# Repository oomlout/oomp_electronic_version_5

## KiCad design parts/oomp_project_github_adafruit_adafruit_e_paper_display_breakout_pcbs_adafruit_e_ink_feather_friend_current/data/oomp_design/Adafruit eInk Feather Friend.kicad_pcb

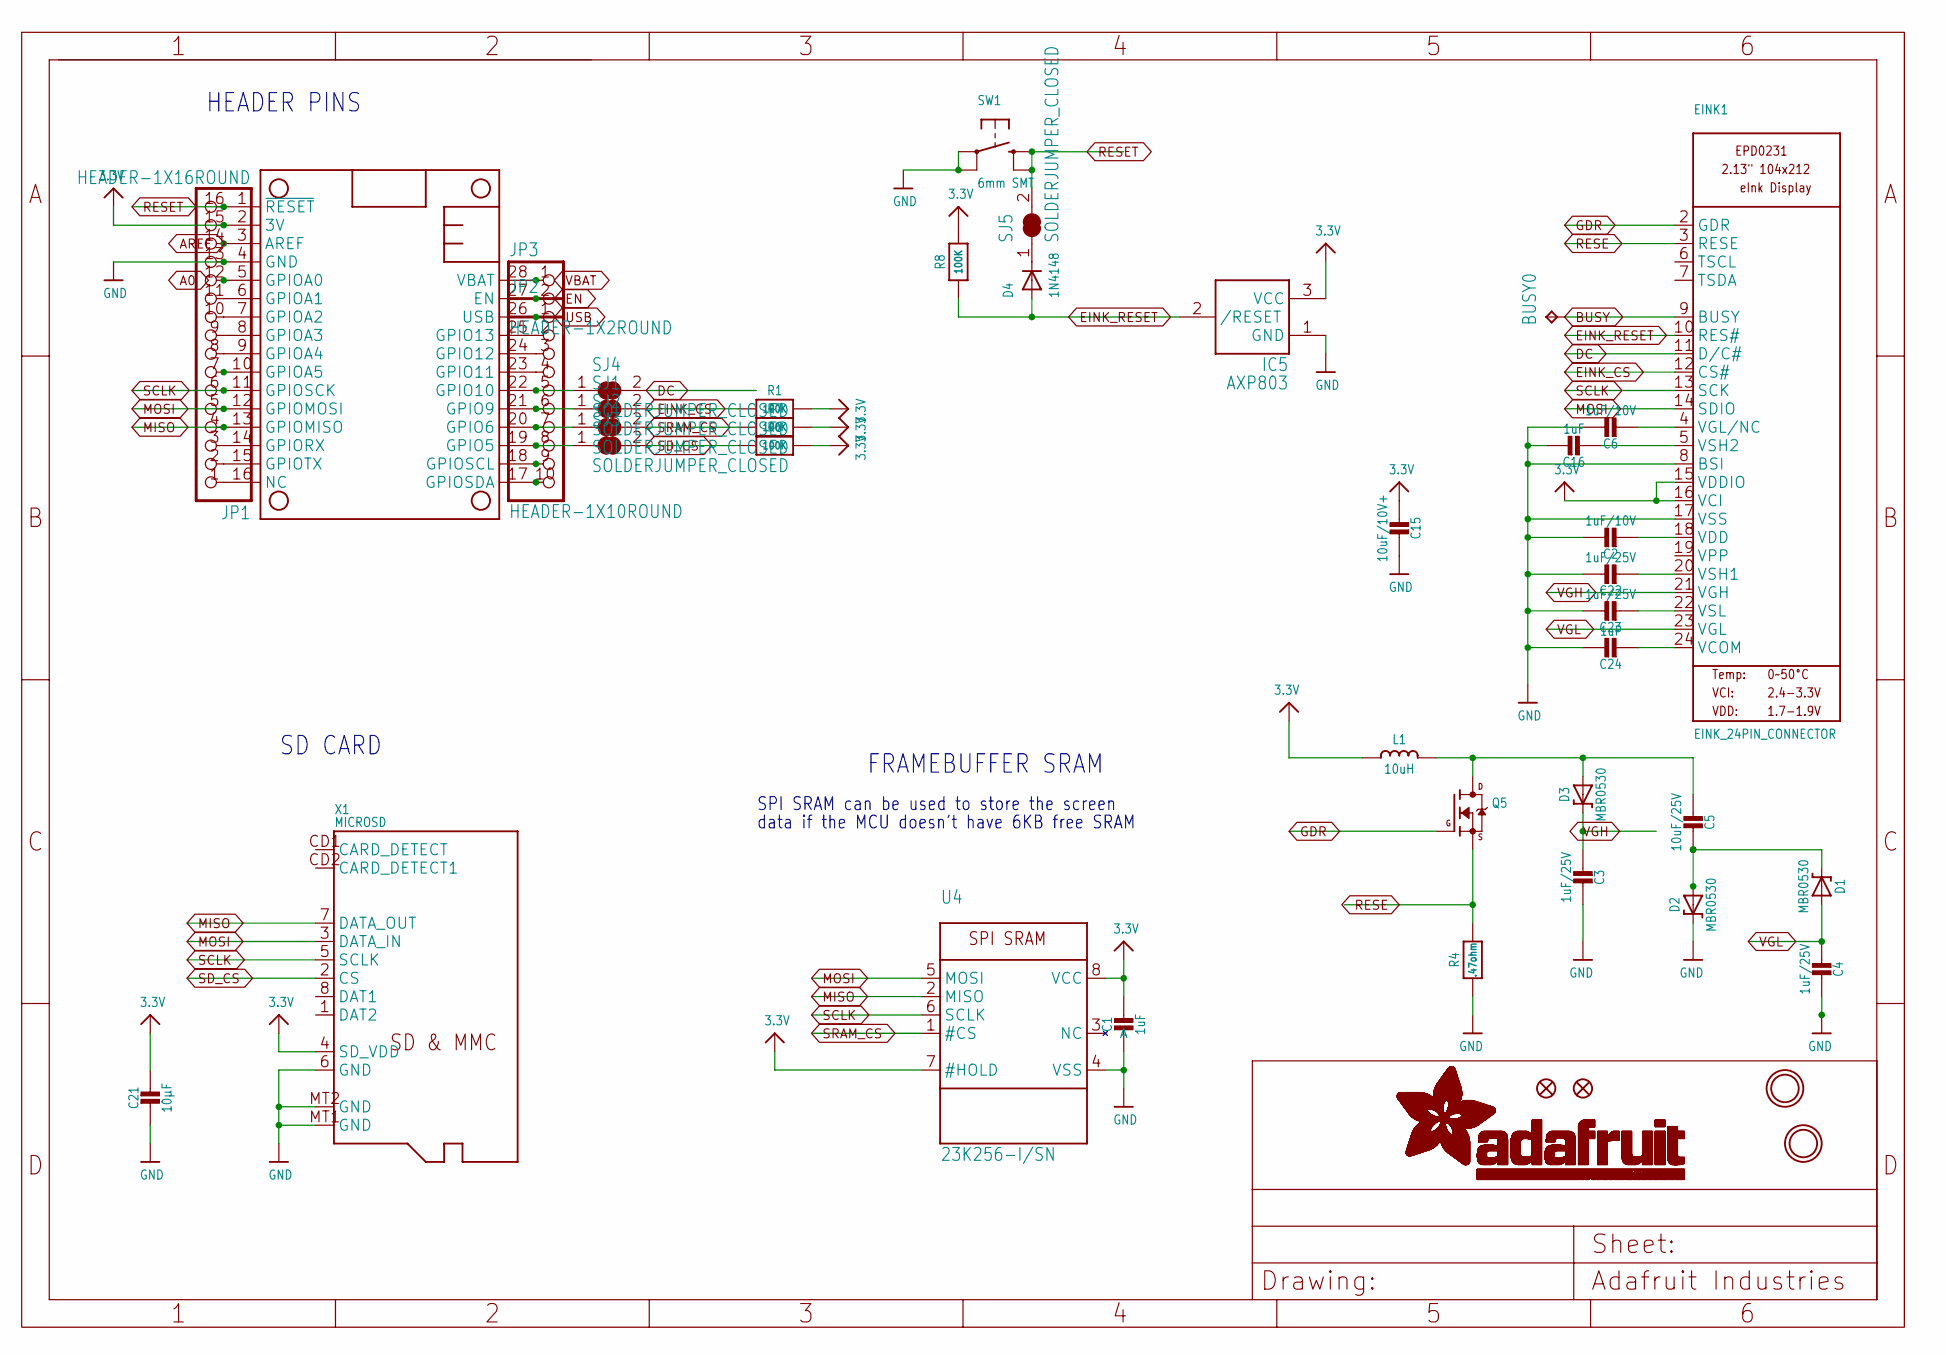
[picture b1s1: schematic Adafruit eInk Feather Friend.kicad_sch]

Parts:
BUSY0: TPTP15SQ; TP15SQ
C1: 1uF; 0805_10MGAP
C2, C6: 1uF/10V; 0805-NO
C3, C4, C22, C23: 1uF/25V; 0805-NO
C5: 10uF/25V; 0805-NO
C15: 10uF/10V+; 0805-NO
C16, C24: 1uF; 0805-NO
C21: 10µF; 0805-NO
D1, D2, D3: MBR0530; SOD-123
D4: 1N4148; SOD-323F
EINK1: EINK_24PIN_CONNECTOR; EINK_24PIN
FID1, FID3: FIDUCIAL_1MM
IC5: AXP803; SOT23
JP1: HEADER-1X16ROUND; 1X16_ROUND
JP2: HEADER-1X10ROUND; 1X10_ROUND
JP3: HEADER-1X2ROUND; 1X02_ROUND
L1: 10uH; INDUCTOR_4X4MM_NR401
MS1: FEATHERWING_NOHOLES
Q5: IRLML0100; SOT23-3
R1, R6, R7, R8: 100K; 0603-NO
R4: .47ohm; 0805_10MGAP
SJ1, SJ2, SJ3, SJ4, SJ5: SOLDERJUMPER_CLOSED; SOLDERJUMPER_CLOSEDWIRE
SW1: 6mm SMT; BTN_KMR2_4.6X2.8
U4: 23K256-I/SN; SOIC8_150MIL
U$3, U$4: MOUNTINGHOLE2.5; MOUNTINGHOLE_2.5_PLATED
X1: MICROSD

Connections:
3.3V: C1.1, C15.2, C21.1, EINK1.15 (VDDIO), EINK1.16 (VCI), IC5.3 (VCC), JP1.15, L1.P$2 (2), MS1.2 (3V), R1.2, R6.2, R7.2, R8.2, U4.7 (#HOLD), U4.8 (VCC), X1.4 (SD_VDD)
A0: JP1.12, MS1.5 (GPIOA0)
AREF: JP1.14, MS1.3 (AREF)
BUSY: BUSY0.TP, EINK1.9 (BUSY)
DC: EINK1.11 (D/C#), SJ4.2
EINK_CS: EINK1.12 (CS#), R1.1, SJ1.2
EINK_RESET: D4.A, EINK1.10 (RES#), IC5.2 (/RESET), R8.1
EN: JP3.2, MS1.27 (EN)
GDR: EINK1.2 (GDR), Q5.1 (G)
GND: C1.2, C2.1, C3.2, C4.2, C6.1, C15.1, C16.1, C21.2, C22.1, C23.1, C24.1, D2.C, EINK1.8 (BSI), EINK1.17 (VSS), IC5.1 (GND), JP1.13, MS1.4 (GND), R4.2, SW1.A, SW1.A' (P1), U4.4 (VSS), X1.6 (GND), X1.MT1 (GND), X1.MT2 (GND)
H: JP2.8, MS1.19 (GPIO5), SJ3.1
I: JP2.7, MS1.20 (GPIO6), SJ2.1
J: JP2.6, MS1.21 (GPIO9), SJ1.1
K: JP2.5, MS1.22 (GPIO10), SJ4.1
MISO: JP1.4, MS1.13 (GPIOMISO), U4.2 (MISO), X1.7 (DATA_OUT)
MOSI: EINK1.14 (SDIO), JP1.5, MS1.12 (GPIOMOSI), U4.5 (MOSI), X1.3 (DATA_IN)
unnamed: JP1.7, MS1.10 (GPIOA5)
unnamed: C5.2, D1.C, D2.A
unnamed: C5.1, D3.A, L1.P$1 (1), Q5.3 (D)
unnamed: C16.2, EINK1.5 (VSH2)
unnamed: C2.2, EINK1.18 (VDD)
unnamed: C22.2, EINK1.20 (VSH1)
unnamed: D4.C, SJ5.1
unnamed: JP1.11, MS1.6 (GPIOA1)
unnamed: C6.2, EINK1.4 (VGL/NC)
unnamed: JP1.10, MS1.7 (GPIOA2)
unnamed: JP1.9, MS1.8 (GPIOA3)
unnamed: JP1.8, MS1.9 (GPIOA4)
unnamed: JP1.3, MS1.14 (GPIORX)
unnamed: JP1.2, MS1.15 (GPIOTX)
unnamed: JP1.1, MS1.16 (NC)
unnamed: JP2.10, MS1.17 (GPIOSDA)
unnamed: JP2.9, MS1.18 (GPIOSCL)
unnamed: JP2.4, MS1.23 (GPIO11)
unnamed: JP2.3, MS1.24 (GPIO12)
unnamed: JP2.2, MS1.25 (GPIO13)
unnamed: C23.2, EINK1.22 (VSL)
unnamed: C24.2, EINK1.24 (VCOM)
RESE: EINK1.3 (RESE), Q5.2 (S), R4.1
RESET: JP1.16, MS1.1 (~RESET), SJ5.2, SW1.B (S), SW1.B' (S1)
SCLK: EINK1.13 (SCK), JP1.6, MS1.11 (GPIOSCK), U4.6 (SCLK), X1.5 (SCLK)
SD_CS: R6.1, SJ3.2, X1.2 (CS)
SRAM_CS: R7.1, SJ2.2, U4.1 (#CS)
USB: JP2.1, MS1.26 (USB)
VBAT: JP3.1, MS1.28 (VBAT)
VGH: C3.1, D3.C, EINK1.21 (VGH)
VGL: C4.1, D1.A, EINK1.23 (VGL)

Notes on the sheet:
FRAMEBUFFER SRAM
SPI SRAM can be used to store the screen
data if the MCU doesn't have 6KB free SRAM
HEADER PINS
SD CARD

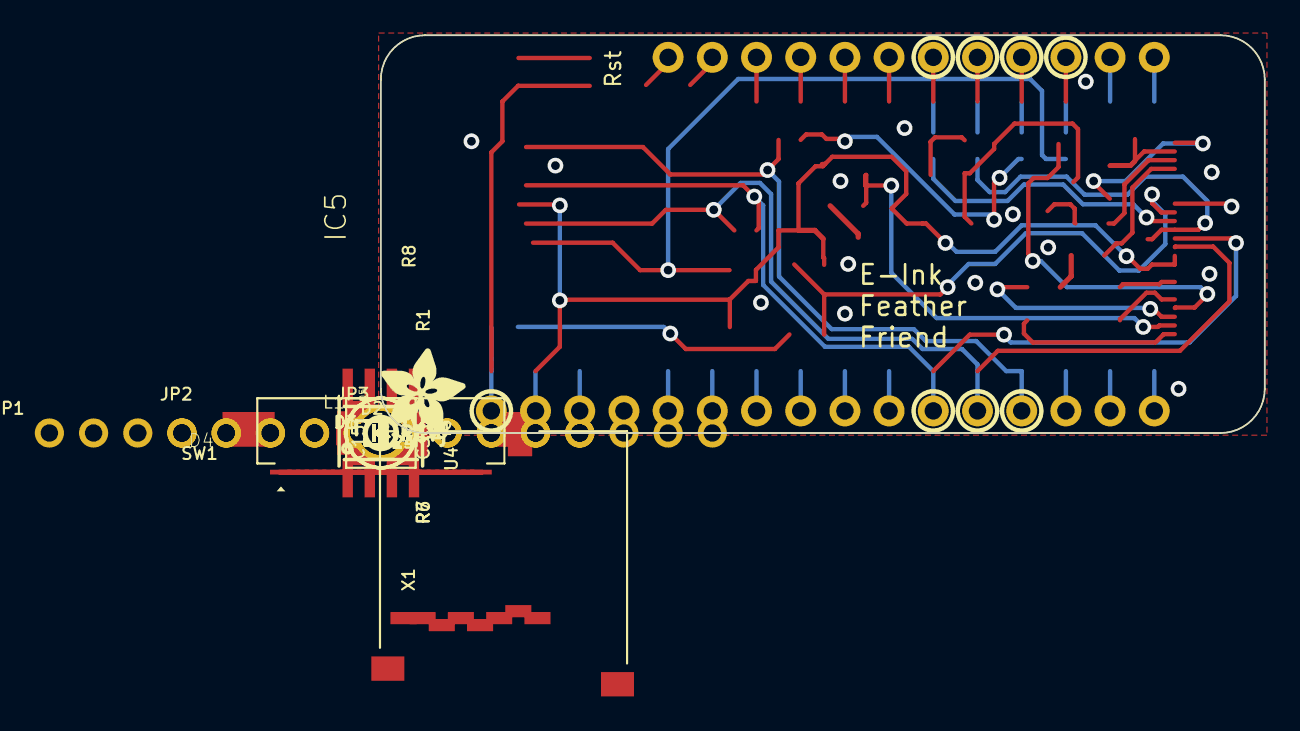
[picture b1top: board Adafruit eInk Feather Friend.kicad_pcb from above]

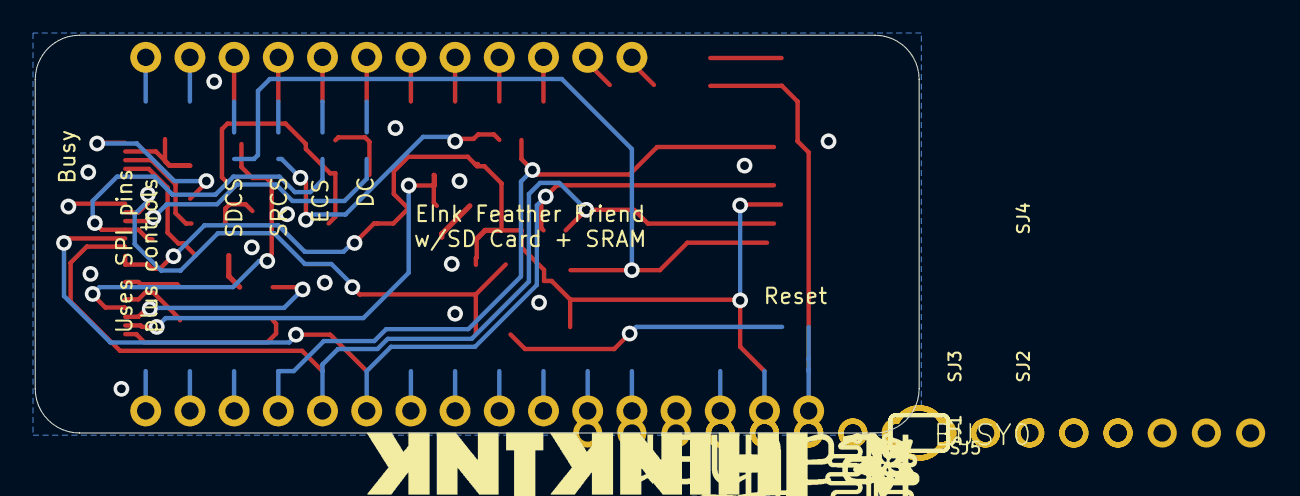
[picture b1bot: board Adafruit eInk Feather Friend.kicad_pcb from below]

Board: 2 copper layers, 50.8 x 22.9 mm, 47 parts (9 on the bottom side), 47 nets.

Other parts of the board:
U$5: THINKINK_1.25IN
U$6: FEATHERLOGO_MED
U$8: ADAFRUIT_5MM
U$9: PCBFEAT-REV-040
U$17: ADAFRUIT_3.5MM

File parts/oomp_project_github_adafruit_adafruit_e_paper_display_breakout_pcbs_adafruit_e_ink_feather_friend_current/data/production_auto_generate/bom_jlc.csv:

Comment,Designator,Footprint,LCSC Part #
,JP3,Adafruit eInk Feather Friend-import-fps:1X02_ROUND,C492401
,JP2,Adafruit eInk Feather Friend-import-fps:1X10_ROUND,C57369
,JP1,Adafruit eInk Feather Friend-import-fps:1X16_ROUND,C7501270
,U$17,Adafruit eInk Feather Friend-import-fps:ADAFRUIT_3.5MM,
,U$8,Adafruit eInk Feather Friend-import-fps:ADAFRUIT_5MM,
,U$6,Adafruit eInk Feather Friend-import-fps:FEATHERLOGO_MED,
,U$9,Adafruit eInk Feather Friend-import-fps:PCBFEAT-REV-040,
,U$5,Adafruit eInk Feather Friend-import-fps:THINKINK_1.25IN,
.47ohm,R4,Adafruit eInk Feather Friend-import-fps:0805_10MGAP,
100K,"R1,R6,R7,R8",Adafruit eInk Feather Friend-import-fps:0603-NO,C25803
10uF/10V+,C15,Adafruit eInk Feather Friend-import-fps:0805-NO,
10uF/25V,C5,Adafruit eInk Feather Friend-import-fps:0805-NO,
10uH,L1,Adafruit eInk Feather Friend-import-fps:INDUCTOR_4X4MM_NR401,
10µF,C21,Adafruit eInk Feather Friend-import-fps:0805-NO,
1N4148,D4,Adafruit eInk Feather Friend-import-fps:SOD-323F,
1uF,"C16,C24",Adafruit eInk Feather Friend-import-fps:0805-NO,
1uF,C1,Adafruit eInk Feather Friend-import-fps:0805_10MGAP,
1uF/10V,"C2,C6",Adafruit eInk Feather Friend-import-fps:0805-NO,
1uF/25V,"C3,C4,C22,C23",Adafruit eInk Feather Friend-import-fps:0805-NO,
23K256-I/SN,U4,Adafruit eInk Feather Friend-import-fps:SOIC8_150MIL,
6mm SMT,SW1,Adafruit eInk Feather Friend-import-fps:BTN_KMR2_4.6X2.8,
AXP803,IC5,Adafruit eInk Feather Friend-import-fps:SOT23,
EINK_24PIN_CONNECTOR,EINK1,Adafruit eInk Feather Friend-import-fps:EINK_24PIN,
FEATHERWING_NOHOLES,MS1,Adafruit eInk Feather Friend-import-fps:FEATHERWING_NOHOLES,
IRLML0100,Q5,Adafruit eInk Feather Friend-import-fps:SOT23-3,
MBR0530,"D1,D2,D3",Adafruit eInk Feather Friend-import-fps:SOD-123,
MICROSD,X1,Adafruit eInk Feather Friend-import-fps:MICROSD,
TPTP15SQ,BUSY0,Adafruit eInk Feather Friend-import-fps:TP15SQ,

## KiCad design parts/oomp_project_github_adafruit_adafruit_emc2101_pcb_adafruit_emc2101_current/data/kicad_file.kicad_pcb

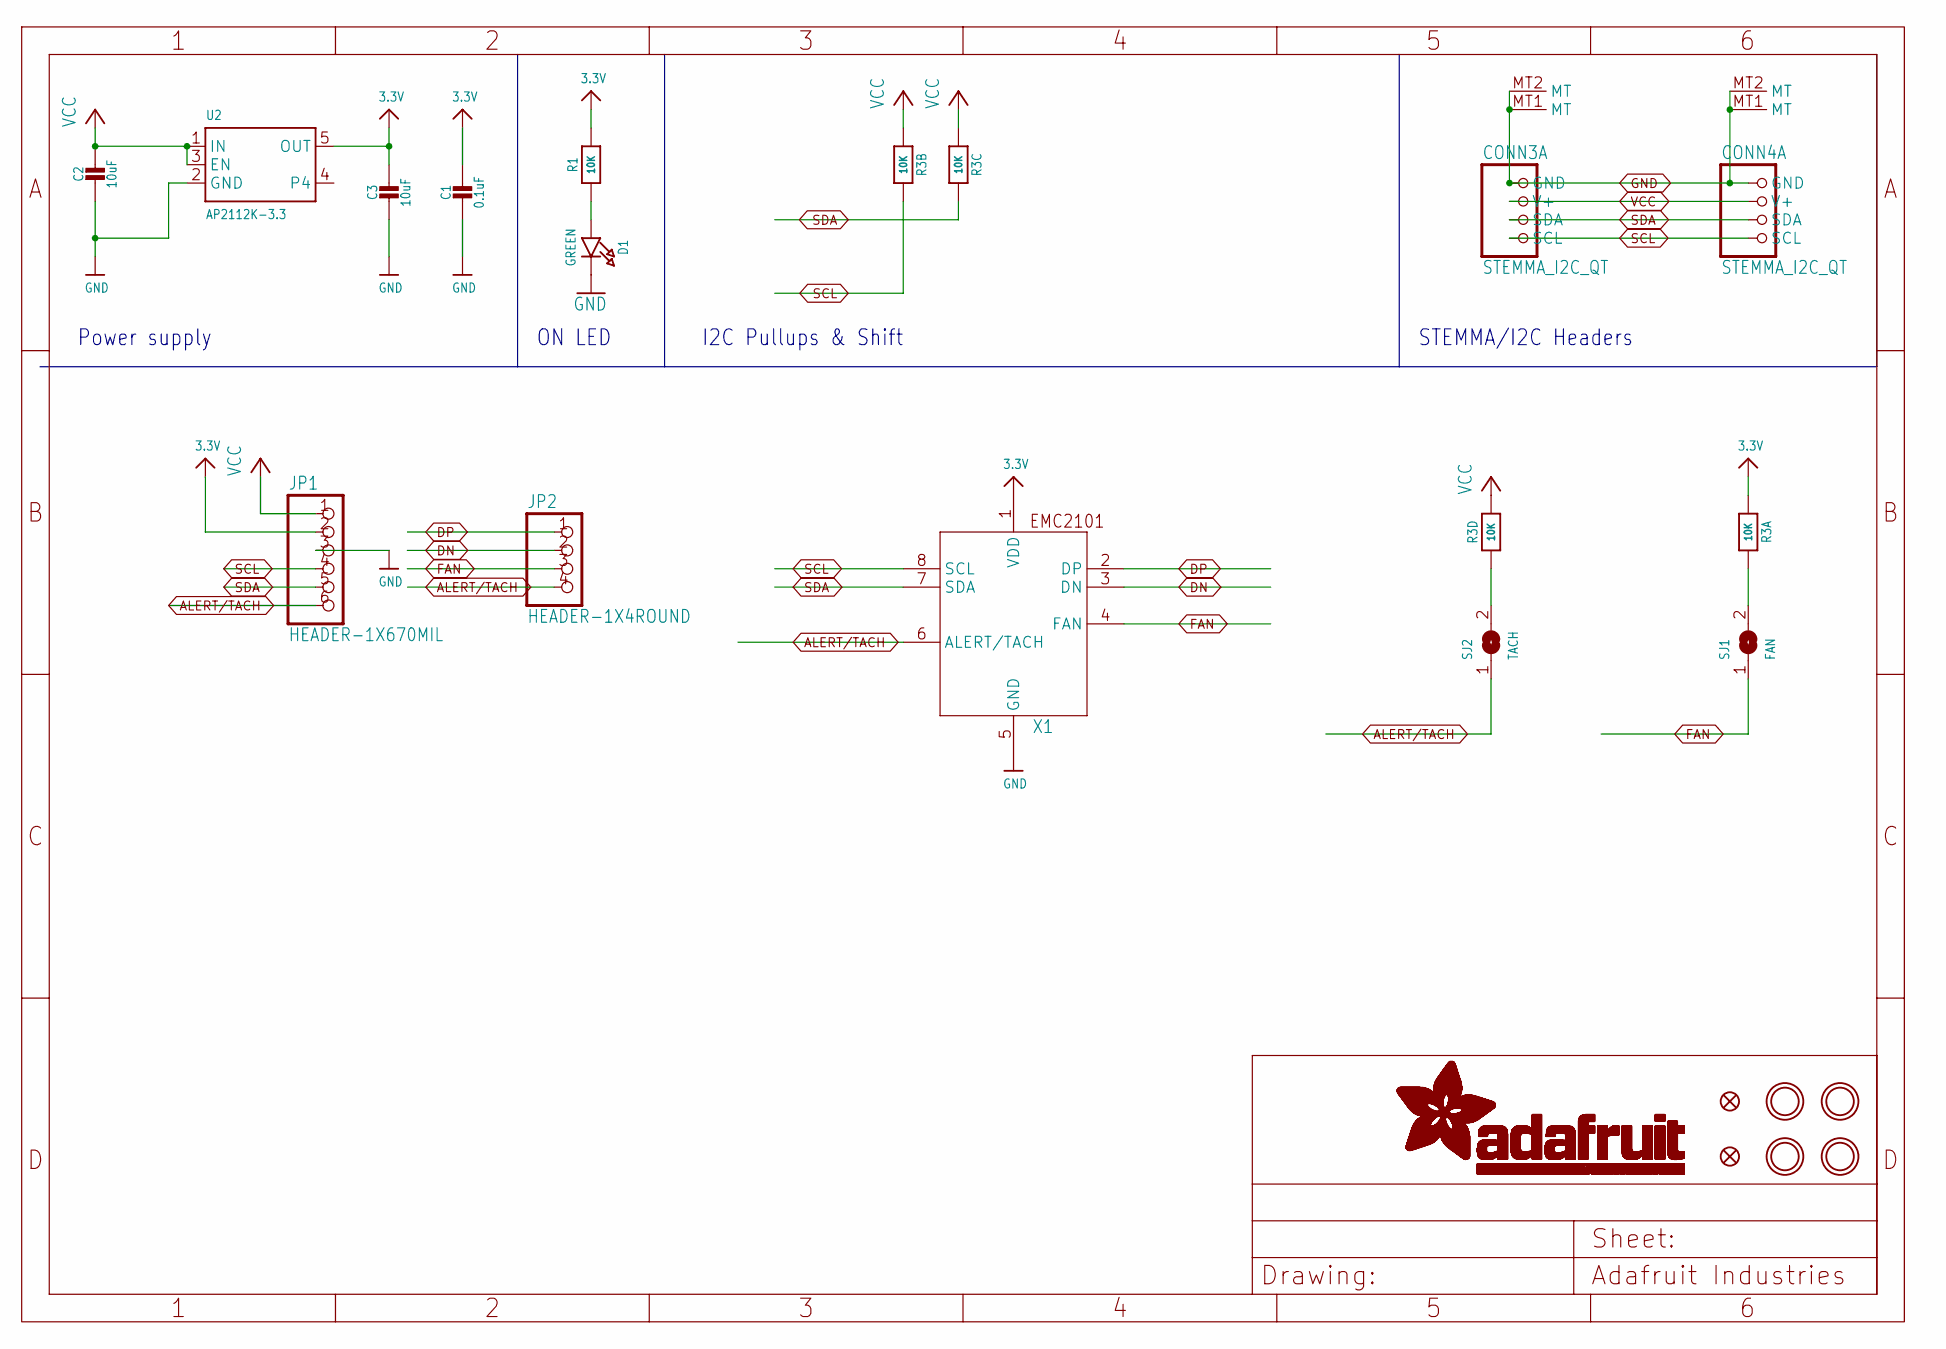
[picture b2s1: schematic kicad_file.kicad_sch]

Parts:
C1: 0.1uF; 0603-NO
C2, C3: 10uF; 0805-NO
CONN3, CONN4: STEMMA_I2C_QT; JST_SH4
D1: GREEN; CHIPLED_0603_NOOUTLINE
FID3, FID4: FIDUCIAL_1MM
JP1: HEADER-1X670MIL; 1X06_ROUND_70
JP2: HEADER-1X4ROUND; 1X04_ROUND
R1: 10K; _0603MP
R3: 10K; RESPACK_4X0603
SJ1: FAN; SOLDERJUMPER_CLOSEDWIRE
SJ2: TACH; SOLDERJUMPER_ARROW_NOPASTE
U2: AP2112K-3.3; SOT23-5
U$1, U$17, U$19, U$21: MOUNTINGHOLE2.5; MOUNTINGHOLE_2.5_PLATED
X1: EMC2101-AZCL; MSOP8_0.65MM

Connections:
3.3V: C1.1, C3.1, JP1.2, R1.2, R3.1, U2.5 (OUT), X1.1 (VDD)
ALERT/TACH: JP1.6, JP2.4, SJ2.1, X1.6 (ALERT/TACH)
DN: JP2.2, X1.3 (DN)
DP: JP2.1, X1.2 (DP)
FAN: JP2.3, SJ1.1, X1.4 (FAN)
GND: C1.2, C2.2, C3.2, CONN3.1 (GND), CONN3.MT1 (MT), CONN3.MT2 (MT), CONN4.1 (GND), CONN4.MT1 (MT), CONN4.MT2 (MT), D1.C, JP1.3, U2.2 (GND), X1.5 (GND)
unnamed: R3.4 (1), SJ2.2
unnamed: R3.8 (2), SJ1.2
unnamed: D1.A, R1.1
SCL: CONN3.4 (SCL), CONN4.4 (SCL), JP1.4, R3.7 (2), X1.8 (SCL)
SDA: CONN3.3 (SDA), CONN4.3 (SDA), JP1.5, R3.6 (2), X1.7 (SDA)
VCC: C2.1, CONN3.2 (V+), CONN4.2 (V+), JP1.1, R3.2 (1), R3.3 (1), R3.5 (2), U2.1 (IN), U2.3 (EN)

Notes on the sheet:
I2C Pullups & Shift
ON LED
STEMMA/I2C Headers
Power supply

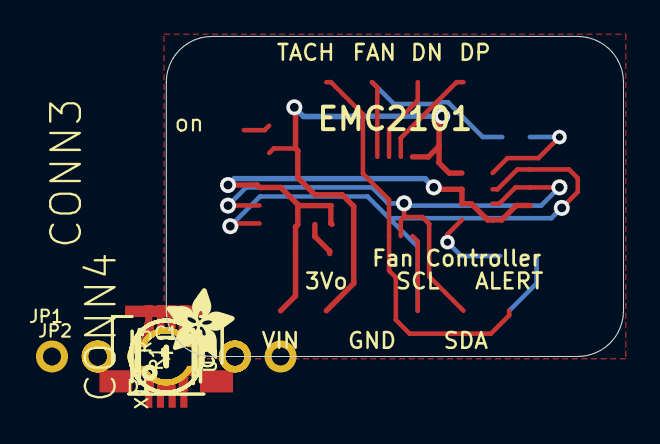
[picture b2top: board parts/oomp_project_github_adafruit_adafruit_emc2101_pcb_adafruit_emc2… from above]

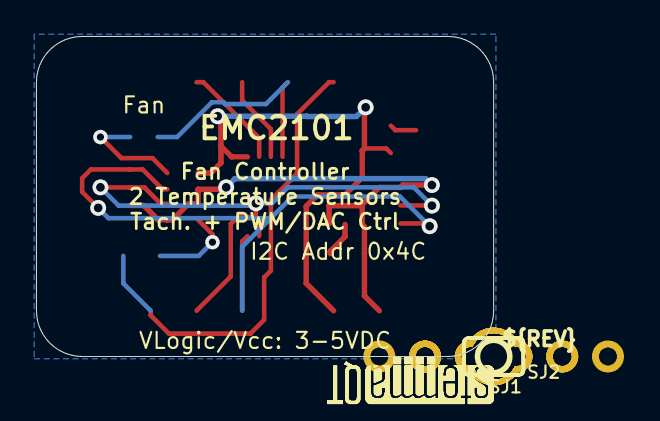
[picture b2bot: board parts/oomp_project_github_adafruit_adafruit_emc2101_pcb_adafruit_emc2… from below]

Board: 2 copper layers, 25.4 x 17.8 mm, 24 parts (5 on the bottom side), 12 nets.

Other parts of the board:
U$22: ADAFRUIT_3.5MM
U$25: PCBFEAT-REV-040
U$30, U$31: STEMMAQT

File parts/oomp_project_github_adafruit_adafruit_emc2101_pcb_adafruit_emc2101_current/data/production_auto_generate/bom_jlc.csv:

Comment,Designator,Footprint,LCSC Part #
,JP2,Adafruit_EMC2101-import-fps:1X04_ROUND,C42431795
,JP1,Adafruit_EMC2101-import-fps:1X06_ROUND_70,C37208
,U$22,Adafruit_EMC2101-import-fps:ADAFRUIT_3.5MM,
,U$25,Adafruit_EMC2101-import-fps:PCBFEAT-REV-040,
,"U$30,U$31",Adafruit_EMC2101-import-fps:STEMMAQT,
0.1uF,C1,Adafruit_EMC2101-import-fps:0603-NO,C14663
10K,R1,Adafruit_EMC2101-import-fps:_0603MP,C98220
10K,R3,Adafruit_EMC2101-import-fps:RESPACK_4X0603,C98220
10uF,"C2,C3",Adafruit_EMC2101-import-fps:0805-NO,
AP2112K-3.3,U2,Adafruit_EMC2101-import-fps:SOT23-5,
EMC2101-AZCL,X1,Adafruit_EMC2101-import-fps:MSOP8_0.65MM,
GREEN,D1,Adafruit_EMC2101-import-fps:CHIPLED_0603_NOOUTLINE,
STEMMA_I2C_QT,"CONN3,CONN4",Adafruit_EMC2101-import-fps:JST_SH4,C160404

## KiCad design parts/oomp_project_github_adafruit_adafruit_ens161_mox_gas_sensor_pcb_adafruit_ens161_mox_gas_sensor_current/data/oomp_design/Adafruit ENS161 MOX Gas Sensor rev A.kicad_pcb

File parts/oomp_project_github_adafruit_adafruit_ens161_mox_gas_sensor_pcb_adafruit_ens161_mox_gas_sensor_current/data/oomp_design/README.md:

# OOMP KiCad design copy

Open `Adafruit ENS161 MOX Gas Sensor rev A.kicad_pro` (or the `.kicad_pcb` / `.kicad_sch`) in KiCad. Local OOMP libraries are under `libraries/`. Original inputs are preserved in [../original/](../original/).

Only verified unchanged installed KiCad defaults were renamed. Modified, custom, unmatched and unavailable items remain unchanged. Soldering variants are never swapped during conversion. Existing pad coordinates, nets and UUIDs are preserved.

See [conversion_report.yaml](conversion_report.yaml) for every conversion and skip. Copy this directory before editing; regeneration refuses to overwrite edited design files.

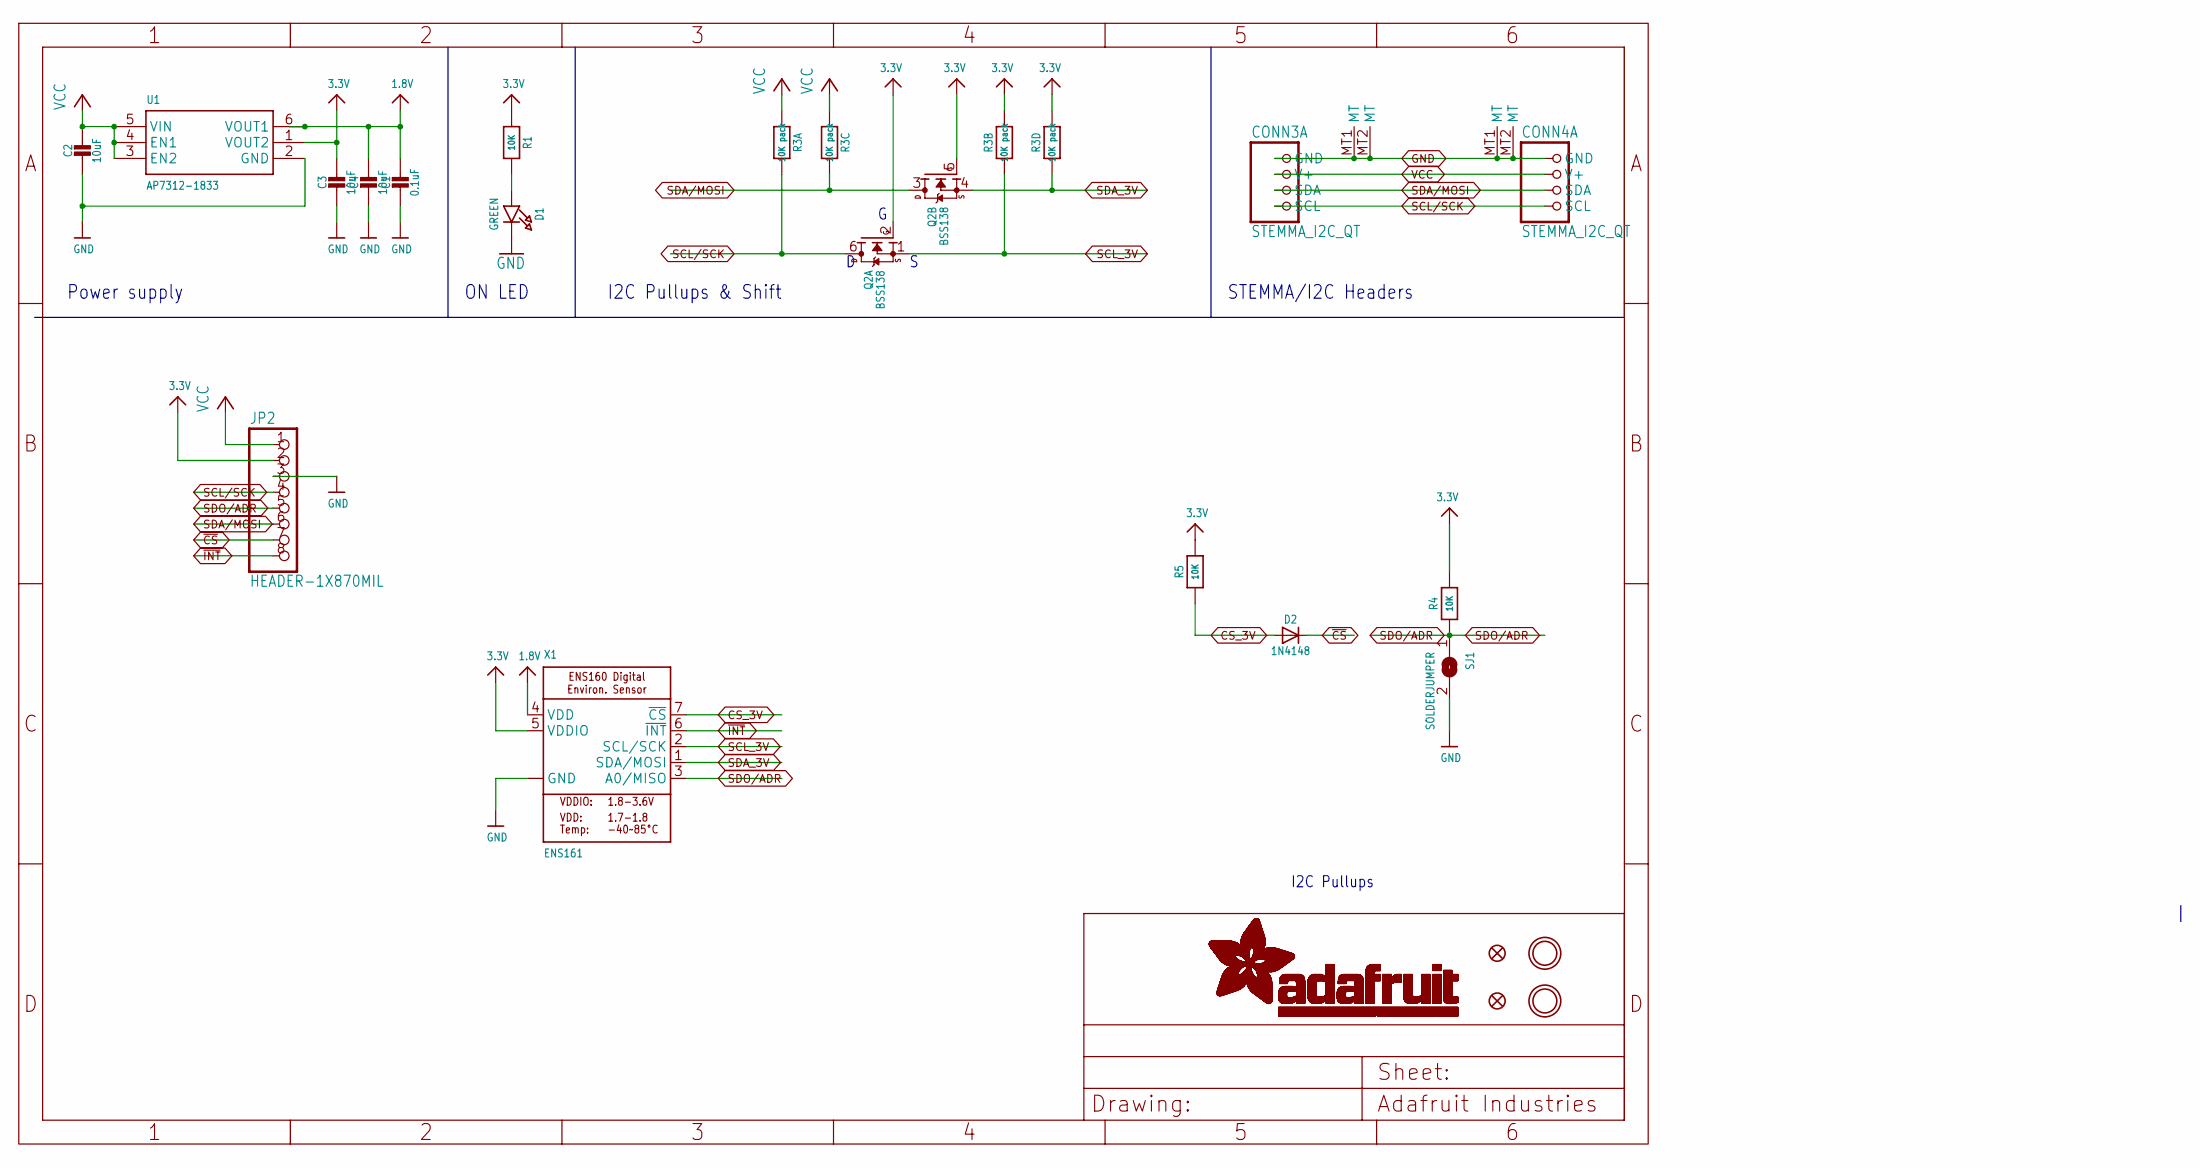
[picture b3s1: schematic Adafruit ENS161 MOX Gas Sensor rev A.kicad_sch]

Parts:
C1: 0.1uF; 0603-NO
C2, C3, C4: 10uF; 0805-NO
CONN3, CONN4: STEMMA_I2C_QT; JST_SH4; LCSC C2845363
D1: GREEN; CHIPLED_0603_NOOUTLINE
D2: 1N4148; SOD-323
FID3, FID4: FIDUCIAL_0.5MM
JP2: HEADER-1X870MIL; 1X08_ROUND_70
Q2: BSS138; SOT363; JLC_ROTATION 270
R1, R4, R5: 10K; 0603-NO
R3: 10K pack; RESPACK_4X0603
SJ1: SOLDERJUMPER; SOLDERJUMPER_ARROW_NOPASTE
U1: AP7312-1833; SOT23-6
U$1, U$17: MOUNTINGHOLE2.5; MOUNTINGHOLE_2.5_PLATED
X1: ENS161; ENS160

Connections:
1.8V: C1.1, C4.1, U1.6 (VOUT1), X1.4 (VDD)
3.3V: C3.1, JP2.2, Q2.2 (G), Q2.5 (G), R1.1, R3.2 (1), R3.4 (1), R4.2, R5.2, U1.1 (VOUT2), X1.5 (VDDIO)
CS_3V: D2.A, R5.1, X1.7 (~CS)
GND: C1.2, C2.2, C3.2, C4.2, CONN3.1 (GND), CONN3.MT1 (MT), CONN3.MT2 (MT), CONN4.1 (GND), CONN4.MT1 (MT), CONN4.MT2 (MT), D1.C, JP2.3, SJ1.2, U1.2 (GND), X1.8 (GND), X1.9 (GND)
unnamed: D1.A, R1.2
SCL/SCK: CONN3.4 (SCL), CONN4.4 (SCL), JP2.4, Q2.6 (D), R3.8 (2)
SCL_3V: Q2.1 (S), R3.7 (2), X1.2 (SCL/SCK)
SDA/MOSI: CONN3.3 (SDA), CONN4.3 (SDA), JP2.6, Q2.3 (D), R3.6 (2)
SDA_3V: Q2.4 (S), R3.5 (2), X1.1 (SDA/MOSI)
SDO/ADR: JP2.5, R4.1, SJ1.1, X1.3 (A0/MISO)
VCC: C2.1, CONN3.2 (V+), CONN4.2 (V+), JP2.1, R3.1, R3.3 (1), U1.3 (EN2), U1.4 (EN1), U1.5 (VIN)
~CS: D2.C, JP2.7
~INT: JP2.8, X1.6 (~INT)

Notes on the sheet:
Power supply
ON LED
I2C Pullups & Shift
STEMMA/I2C Headers
I2C Pullups

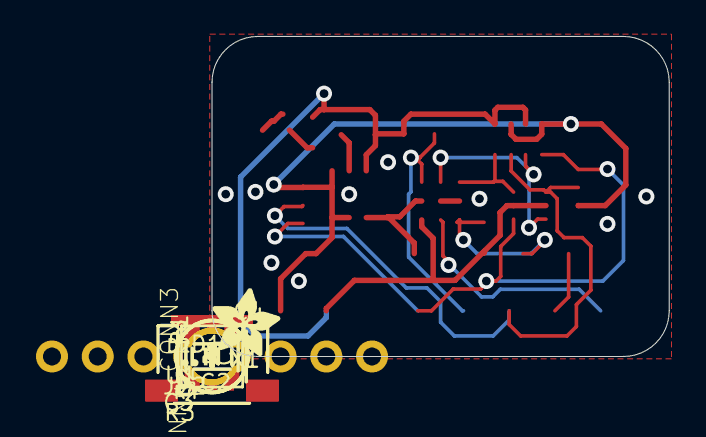
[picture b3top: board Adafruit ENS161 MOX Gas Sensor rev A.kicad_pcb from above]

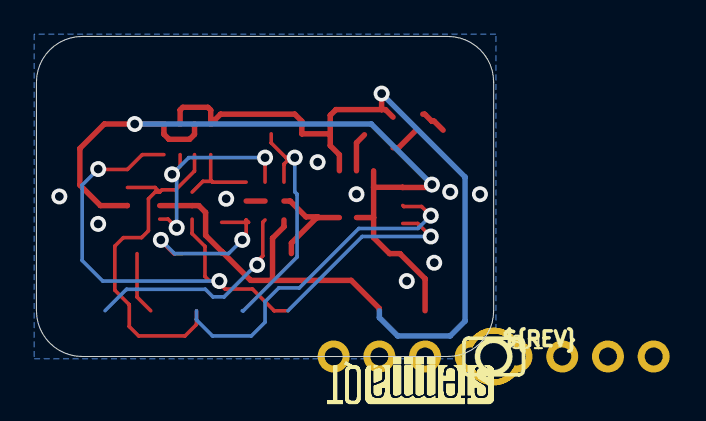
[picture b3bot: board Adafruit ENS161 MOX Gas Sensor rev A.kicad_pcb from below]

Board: 2 copper layers, 25.4 x 17.8 mm, 41 parts (9 on the bottom side), 13 nets.

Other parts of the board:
PLABEL0: PLABEL0
PLABEL1: PLABEL1
PLABEL2: PLABEL2
PLABEL3: PLABEL3
PLABEL4: PLABEL4
PLABEL6: PLABEL6
PLABEL7: PLABEL7
PLABEL8: PLABEL8
PLABEL9: PLABEL9
PLABEL10: PLABEL10
PLABEL12: PLABEL12
PLABEL13: PLABEL13
PLABEL14: PLABEL14
PLABEL15: PLABEL15
PLABEL16: PLABEL16
PLABEL17: PLABEL17
U$20: ADAFRUIT_3.5MM
U$25: PCBFEAT-REV-040
U$30, U$31: STEMMAQT

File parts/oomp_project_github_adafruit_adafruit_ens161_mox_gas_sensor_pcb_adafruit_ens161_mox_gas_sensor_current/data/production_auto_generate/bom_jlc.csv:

Comment,Designator,Footprint,LCSC Part #
,JP2,Adafruit ENS161 MOX Gas Sensor rev A-import-fps:1X08_ROUND_70,C492421
,U$20,Adafruit ENS161 MOX Gas Sensor rev A-import-fps:ADAFRUIT_3.5MM,
,U$25,Adafruit ENS161 MOX Gas Sensor rev A-import-fps:PCBFEAT-REV-040,
,PLABEL0,Adafruit ENS161 MOX Gas Sensor rev A-import-fps:PLABEL0,
,PLABEL1,Adafruit ENS161 MOX Gas Sensor rev A-import-fps:PLABEL1,
,PLABEL10,Adafruit ENS161 MOX Gas Sensor rev A-import-fps:PLABEL10,
,PLABEL12,Adafruit ENS161 MOX Gas Sensor rev A-import-fps:PLABEL12,
,PLABEL13,Adafruit ENS161 MOX Gas Sensor rev A-import-fps:PLABEL13,
,PLABEL14,Adafruit ENS161 MOX Gas Sensor rev A-import-fps:PLABEL14,
,PLABEL15,Adafruit ENS161 MOX Gas Sensor rev A-import-fps:PLABEL15,
,PLABEL16,Adafruit ENS161 MOX Gas Sensor rev A-import-fps:PLABEL16,
,PLABEL17,Adafruit ENS161 MOX Gas Sensor rev A-import-fps:PLABEL17,
,PLABEL2,Adafruit ENS161 MOX Gas Sensor rev A-import-fps:PLABEL2,
,PLABEL3,Adafruit ENS161 MOX Gas Sensor rev A-import-fps:PLABEL3,
,PLABEL4,Adafruit ENS161 MOX Gas Sensor rev A-import-fps:PLABEL4,
,PLABEL6,Adafruit ENS161 MOX Gas Sensor rev A-import-fps:PLABEL6,
,PLABEL7,Adafruit ENS161 MOX Gas Sensor rev A-import-fps:PLABEL7,
,PLABEL8,Adafruit ENS161 MOX Gas Sensor rev A-import-fps:PLABEL8,
,PLABEL9,Adafruit ENS161 MOX Gas Sensor rev A-import-fps:PLABEL9,
,"U$30,U$31",Adafruit ENS161 MOX Gas Sensor rev A-import-fps:STEMMAQT,
0.1uF,C1,Adafruit ENS161 MOX Gas Sensor rev A-import-fps:0603-NO,C14663
10K,"R1,R4,R5",Adafruit ENS161 MOX Gas Sensor rev A-import-fps:0603-NO,C98220
10K pack,R3,Adafruit ENS161 MOX Gas Sensor rev A-import-fps:RESPACK_4X0603,C98220
10uF,"C2,C3,C4",Adafruit ENS161 MOX Gas Sensor rev A-import-fps:0805-NO,
1N4148,D2,Adafruit ENS161 MOX Gas Sensor rev A-import-fps:SOD-323,
AP7312-1833,U1,Adafruit ENS161 MOX Gas Sensor rev A-import-fps:SOT23-6,
BSS138,Q2,Adafruit ENS161 MOX Gas Sensor rev A-import-fps:SOT363,
ENS161,X1,Adafruit ENS161 MOX Gas Sensor rev A-import-fps:ENS160,
GREEN,D1,Adafruit ENS161 MOX Gas Sensor rev A-import-fps:CHIPLED_0603_NOOUTLINE,
STEMMA_I2C_QT,"CONN3,CONN4",Adafruit ENS161 MOX Gas Sensor rev A-import-fps:JST_SH4,C160404
